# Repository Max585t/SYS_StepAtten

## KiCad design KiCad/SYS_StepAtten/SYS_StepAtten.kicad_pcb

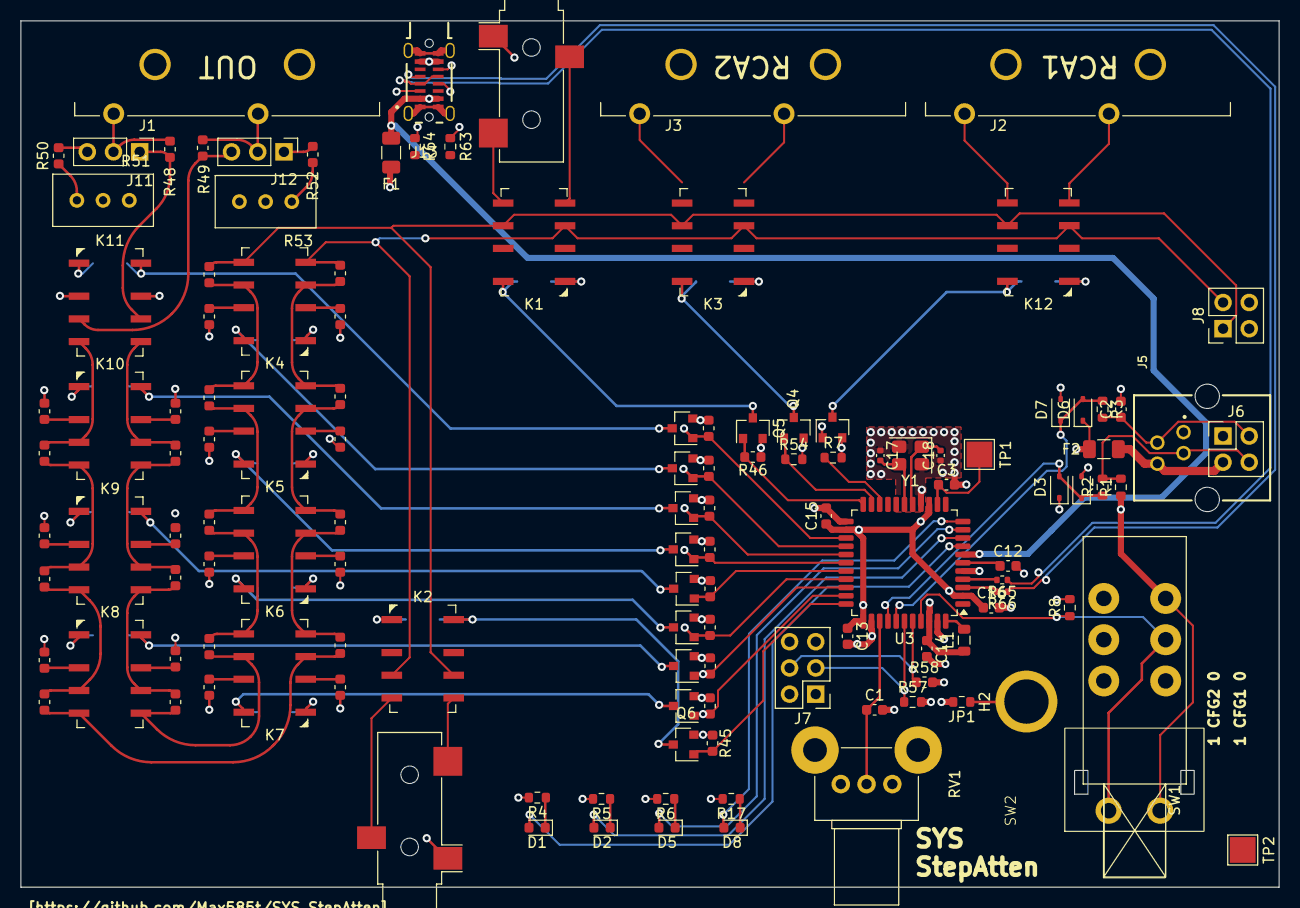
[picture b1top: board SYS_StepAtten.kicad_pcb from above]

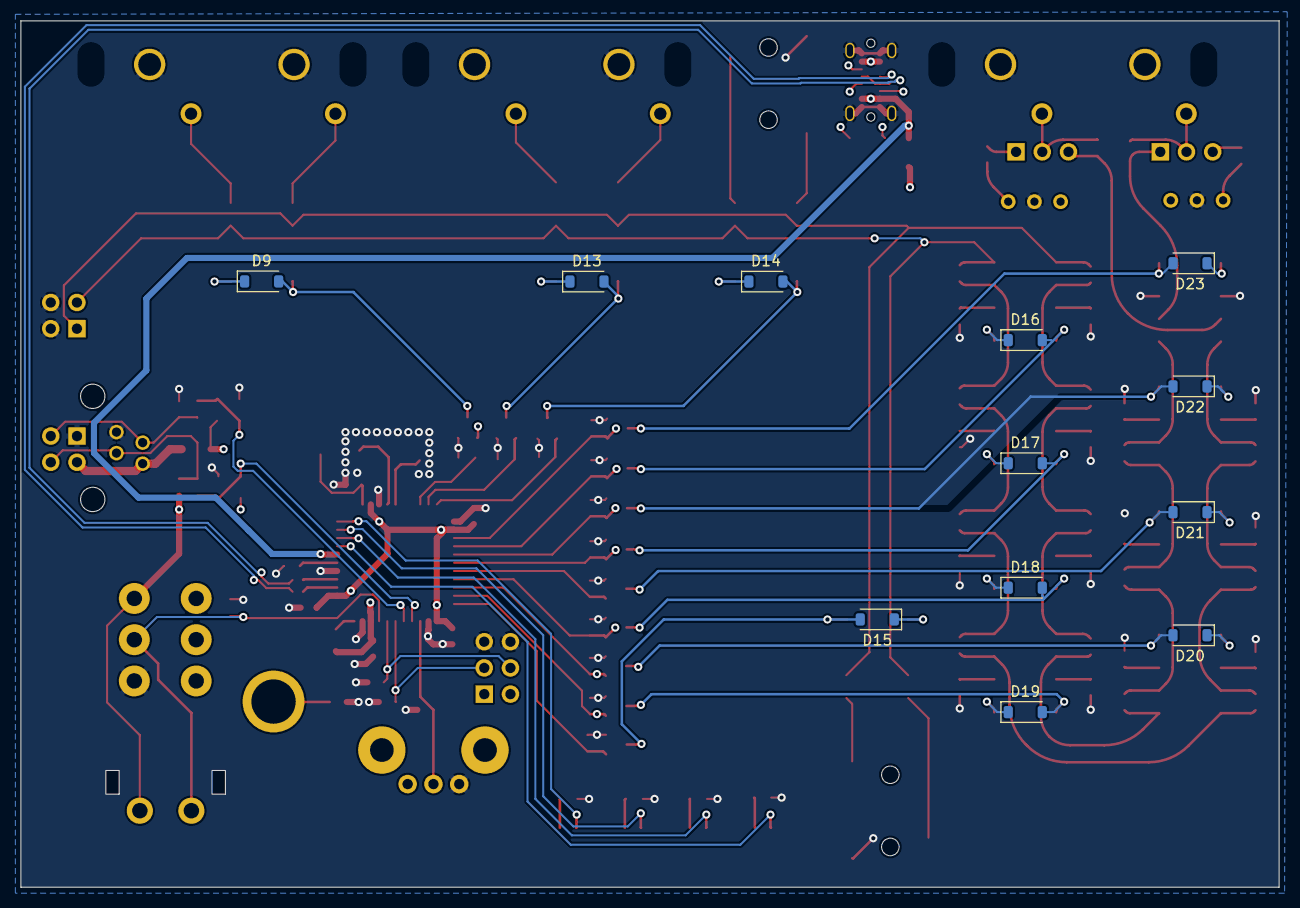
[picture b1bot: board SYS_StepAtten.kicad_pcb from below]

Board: 4 copper layers, 122.0 x 84.0 mm, 138 parts (12 on the bottom side), 102 nets.

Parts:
C1, C2, C3, C13, C14, C16: 0u1; C_0603_1608Metric
C12: 1uf; C_0603_1608Metric
C15: 1u; C_0603_1608Metric
C17, C18: 20pF; C_0402_1005Metric
D1, D2, D5, D8: LED; LED_0603_1608Metric
D3, D4, D6, D7: SD03; D_SOD-323
D9, D13, D14, D15, D16, D17, D18, D19, D20, D21, D22, D23: 1N4001; D_SOD-123
F1: 1A; Fuse_1206_3216Metric
F2: 0.15A; Fuse_1206_3216Metric
H2: MH 1; MountingHole_4.3mm_M4_Pad_Via
J1: RCA-Out; RCA_KobiCon_161-4220-E
J2: RCA-1; RCA_KobiCon_161-4220-E
J3: RCA-2; RCA_KobiCon_161-4220-E
J4, J9: AudioJack3; Jack_3.5mm_CUI_SJ-3523-SMT_Horizontal
J5: RJ9; 615004143821
J6: POT_EXT Conn; PinHeader_2x02_P2.54mm_Vertical
J7: cfg jumper; PinHeader_2x03_P2.54mm_Vertical
J8: Conn_02x02_Odd_Even; PinHeader_2x02_P2.54mm_Vertical
J11: ADJ_L; PinHeader_1x03_P2.54mm_Vertical
J12: ADJ_R; PinHeader_1x03_P2.54mm_Vertical
J13: USB_C_Receptacle_USB2.0_16P; GCT_USB4210-GF-A_REVA
JP1: gnd_case; R_0603_1608Metric
K1, K2, K3, K12: IME03; Relay_2P2T_10x6mm_TE_IMxxG
K4, K5, K6, K7, K8, K9, K10, K11: IM03; Relay_2P2T_10x6mm_TE_IMxxG
L1: MH2029-300Y; L_0805_2012Metric
Q1, Q4, Q5, Q6, Q7, Q8, Q9, Q10, Q11, Q12, Q13, Q14: 2N7002; SOT-23
R1, R7, R8, R34, R35, R36, R37, R40, R41, R44, R45, R46, R47, R54, R57, R58: 10K; R_0603_1608Metric
R2, R3: 100R; R_0603_1608Metric
R4, R5, R6, R17: 500R; R_0603_1608Metric
R9, R10: 261R; R_0603_1608Metric
R11, R12: 9K53; R_0603_1608Metric
R13, R14: 1K87; R_0603_1608Metric
R15, R16: 8K25; R_0603_1608Metric
R18, R19: 6K49; R_0603_1608Metric
R20, R21: 5K9; R_0603_1608Metric
R22, R23: 18K; R_0603_1608Metric
R24, R25: 3K6; R_0603_1608Metric
R26, R27: 39K; R_0603_1608Metric
R28, R29: 2K; R_0603_1608Metric
R30, R31: 82K; R_0603_1608Metric
R32, R33: 1K1; R_0603_1608Metric
R38, R39: 160K; R_0603_1608Metric
R42, R43: 560R; R_0603_1608Metric
R48, R49: 0R; R_0603_1608Metric
R50, R52: 12K; R_0603_1608Metric
R51, R53: 5K; Potentiometer_Bourns_3296W_Vertical
R63, R64: 5K1; R_0603_1608Metric
R65, R66: 22R; R_0402_1005Metric
RV1: 10K Linear; Potentiometer_Alps_RK09K_Single_Horizontal
SW1: INPUT_SWITCH; ALPS_SPUN191400
SW2: SW_MEC_5G; Untitled
TP1: nrst; TestPoint_Pad_2.5x2.5mm
TP2: debug; TestPoint_Pad_2.5x2.5mm
U3: ATmega32U4-A; TQFP-44_10x10mm_P0.8mm
Y1: ABM8-16.000MHZ-10-R60-B1U-T; Crystal_SMD_Abracon_ABM8G-4Pin_3.2x2.5mm

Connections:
+5V: C13.1, C14.1, C15.1, C16.1, D3.1 (K), D6.1 (K), D9.1 (K), D13.1 (K), D14.1 (K), D15.1 (K), D16.1 (K), D17.1 (K), D18.1 (K), D19.1 (K), D20.1 (K), D21.1 (K), D22.1 (K), D23.1 (K), F1.1, F2.2, J7.1, J7.2, K1.1, K2.1, K3.1, K4.1, K5.1, K6.1, K7.1, K8.1, K9.1, K10.1, K11.1, K12.1, L1.1, R1.1, RV1.3, SW1.6 (C), SW2.2 (B), U3.2 (UVCC), U3.14 (VCC), U3.24 (AVCC), U3.34 (VCC), U3.42 (AREF)
/AUX1_L: J9.T, K1.5
/AUX1_R: J9.R, K1.4
/AUX2_L: J4.T, K2.5
/AUX2_R: J4.R, K2.4
/D+: J13.A6 (D+), J13.B6 (D+), R65.1
/D-: J13.A7 (D-), J13.B7 (D-), R66.1
/L: J8.1, K1.6, K2.6, K3.6, K4.5, K12.6, R11.2
/NRST: C3.1, TP1.1, U3.13 (~RESET)
/R: J8.2, K1.3, K2.3, K3.3, K4.4, K12.3, R12.2
/RCA1_L: J2.2, K12.5
/RCA1_R: J2.4, K12.4
/RCA2_L: J3.2, K3.5
/RCA2_R: J3.4, K3.4
/btn: R8.1, SW1.5 (B), SW2.1 (A), U3.41 (PF0)
/cfg1: J7.3, R57.1, U3.39 (PF4)
/cfg2: J7.4, R58.1, U3.40 (PF1)
/e_p: C2.1, J5.2, J6.2, R3.2
/e_s: J5.3, J6.4, R1.2, R2.2
/extctrl_pot: D6.2 (A), D7.1 (K), R3.1, U3.38 (PF5)
/extctrl_sense: D3.2 (A), D4.1 (K), R2.1, U3.37 (PF6)
/poti: C1.1, RV1.2, U3.36 (PF7)
/rly_atten0: Q13.1 (G), R34.1, U3.27 (PD7)
/rly_atten1: Q12.1 (G), R35.1, U3.29 (PB5)
/rly_atten2: Q11.1 (G), R36.1, U3.31 (PC6)
/rly_atten3: Q10.1 (G), R37.1, U3.32 (PC7)
/rly_atten4: Q9.1 (G), R40.1, U3.30 (PB6)
/rly_atten5: Q8.1 (G), R41.1, U3.28 (PB4)
/rly_atten6: Q7.1 (G), R44.1, U3.26 (PD6)
/rly_mute: Q14.1 (G), R47.1, U3.25 (PD4)
/rly_selectL_1: Q6.1 (G), R45.1, U3.33 (~HWB/PE2)
/rly_selectL_2: Q5.1 (G), R46.1, U3.22 (PD5)
/rly_selectL_3: Q4.1 (G), R54.1, U3.21 (PD3)
/rly_selectL_4: Q1.1 (G), R7.1, U3.20 (PD2)
GND: C1.2, C2.2, C3.2, C12.2, C13.2, C14.2, C15.2, C16.2, C17.1, C18.1, D4.2 (A), D7.2 (A), J1.1, J1.3, J2.1, J2.3, J3.1, J3.3, J4.S, J5.1, J6.1, J7.5, J7.6, J8.3, J8.4, J9.S, J13.A1 (GND), J13.A12 (GND), J13.B1 (GND), J13.B12 (GND), J13.SH1 (SHIELD), J13.SH2 (SHIELD), J13.SH3 (SHIELD), J13.SH4 (SHIELD), JP1.2, K11.2, K11.7, Q1.2 (S), Q4.2 (S), Q5.2 (S), Q6.2 (S), Q7.2 (S), Q8.2 (S), Q9.2 (S), Q10.2 (S), Q11.2 (S), Q12.2 (S), Q13.2 (S), Q14.2 (S), R4.2, R5.2, R6.2, R7.2, R8.2, R9.1, R10.1, R13.1, R14.1, R17.2, R18.1, R19.1, R22.1, R23.1, R26.1, R27.1, R30.1, R31.1, R34.2, R35.2, R36.2, R37.2, R38.1, R39.1, R40.2, R41.2, R44.2, R45.2, R46.2, R47.2, R51.2, R53.2, R54.2, R57.2, R58.2, R63.2, R64.2, RV1.1, SW1.4 (A), U3.5 (UGND), U3.15 (GND), U3.23 (GND), U3.35 (GND), U3.43 (GND), Y1.2, Y1.4
unnamed: D1.2 (A), U3.8 (PB0)
unnamed: D1.1 (K), R4.1
unnamed: D2.2 (A), U3.9 (PB1)
unnamed: D2.1 (K), R5.1
unnamed: D5.2 (A), U3.10 (PB2)
unnamed: D5.1 (K), R6.1
unnamed: D8.2 (A), U3.11 (PB3)
unnamed: D8.1 (K), R17.1
unnamed: D9.2 (A), K12.8, Q1.3 (D)
unnamed: D13.2 (A), K3.8, Q4.3 (D)
unnamed: D14.2 (A), K1.8, Q5.3 (D)
unnamed: D15.2 (A), K2.8, Q6.3 (D)
unnamed: D16.2 (A), K4.8, Q7.3 (D)
unnamed: D17.2 (A), K5.8, Q8.3 (D)
unnamed: D18.2 (A), K6.8, Q9.3 (D)
unnamed: D19.2 (A), K7.8, Q10.3 (D)
unnamed: D20.2 (A), K8.8, Q11.3 (D)
unnamed: D21.2 (A), K9.8, Q12.3 (D)
unnamed: D22.2 (A), K10.8, Q13.3 (D)
unnamed: D23.2 (A), K11.8, Q14.3 (D)
unnamed: H2.1, JP1.1
unnamed: F2.1, J5.4, J6.3
unnamed: J11.1, K11.6, R48.2
unnamed: J1.2, J11.2, R48.1
unnamed: J11.3, R50.1
unnamed: J12.1, R52.1
unnamed: J1.4, J12.2, R49.1
unnamed: J12.3, K11.3, R49.2
unnamed: J13.A5 (CC1), R64.1
unnamed: J13.B5 (CC2), R63.1
unnamed: K4.2, R10.2
unnamed: K4.3, K5.4, R12.1, R16.2
unnamed: K4.6, K5.5, R11.1, R15.2
unnamed: K4.7, R9.2
unnamed: K5.2, R14.2
unnamed: K5.3, K6.4, R16.1, R21.2
unnamed: K5.6, K6.5, R15.1, R20.2
unnamed: K5.7, R13.2
unnamed: K6.2, R19.2
unnamed: K6.3, K7.4, R21.1, R25.2
unnamed: K6.6, K7.5, R20.1, R24.2
unnamed: K6.7, R18.2
unnamed: K7.2, R23.2
unnamed: K7.3, K8.4, R25.1, R29.2
unnamed: K7.6, K8.5, R24.1, R28.2
unnamed: K7.7, R22.2
unnamed: K8.2, R27.2
unnamed: K8.3, K9.4, R29.1, R33.2
unnamed: K8.6, K9.5, R28.1, R32.2
unnamed: K8.7, R26.2
unnamed: K9.2, R31.2
unnamed: K9.7, R30.2
unnamed: K10.2, R39.2
unnamed: K10.3, K11.4, R43.1
unnamed: K9.3, K10.4, R33.1, R43.2
unnamed: K9.6, K10.5, R32.1, R42.2
unnamed: K10.6, K11.5, R42.1
unnamed: K10.7, R38.2
unnamed: L1.2, U3.44 (AVCC)
unnamed: R50.2, R51.1
unnamed: R52.2, R53.1
unnamed: R65.2, U3.4 (D+)
unnamed: R66.2, U3.3 (D-)
unnamed: C12.1, U3.6 (UCAP)
unnamed: C17.2, U3.17 (XTAL1), Y1.3
unnamed: C18.2, U3.16 (XTAL2), Y1.1
VBUS: F1.2, J13.A4 (VBUS), J13.A9 (VBUS), J13.B4 (VBUS), J13.B9 (VBUS), U3.7 (VBUS)

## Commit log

2025-11-09 Change relays and micro and USB c for power
2025-11-10 finished schematic
2025-11-10 add uncommitted changes
2025-11-18 Redo relay layout
2026-06-05 Sync work done on laptop
    finished relay layout
